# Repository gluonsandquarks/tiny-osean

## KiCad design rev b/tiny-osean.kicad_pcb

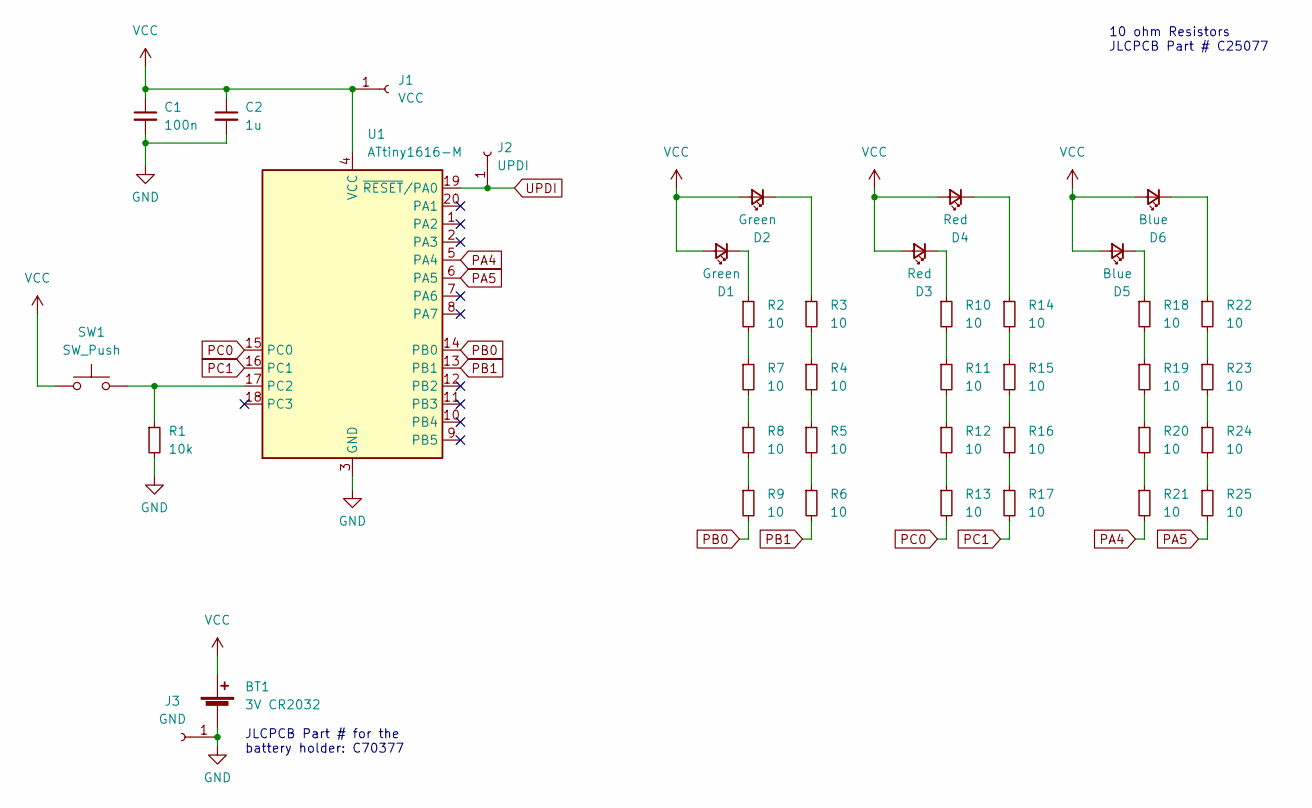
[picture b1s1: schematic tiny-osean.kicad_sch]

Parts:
BT1: 3V CR2032; CR2032 Holder; LCSC C70377
C1: 100n; C_0402_1005Metric; LCSC C307331
C2: 1u; C_0603_1608Metric; LCSC C15849
D1, D2: Green; C_0805_2012Metric_Pad1.18x1.45mm_HandSolder; LCSC C2296
D3, D4: Red; C_0805_2012Metric_Pad1.18x1.45mm_HandSolder; LCSC C2296
D5, D6: Blue; C_0805_2012Metric_Pad1.18x1.45mm_HandSolder; LCSC C2296
J1: VCC; PinHeader_1x01_P2.54mm_Vertical
J2: UPDI; PinHeader_1x01_P2.54mm_Vertical
J3: GND; PinHeader_1x01_P2.54mm_Vertical
R1: 10k; R_0603_1608Metric; LCSC C25804
R2, R3, R4, R5, R6, R7, R8, R9, R10, R11, R12, R13, R14, R15, R16, R17, R18, R19, R20, R21, R22, R23, R24, R25: 10; R_0402_1005Metric; LCSC C25077
SW1: SW_Push; SW_Push_1P1T_NO_CK_KSC6xxJ; LCSC C318884
U1: ATtiny1616-M; VQFN-20-1EP_3x3mm_P0.4mm_EP1.7x1.7mm; LCSC C507118

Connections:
GND: BT1.2 (-), C1.2, C2.2, J3.1, R1.2, U1.3 (GND), U1.21 (GND)
unnamed: D1.1 (K), R2.1
unnamed: D2.1 (K), R3.1
unnamed: D3.1 (K), R10.1
unnamed: D4.1 (K), R14.1
unnamed: D5.1 (K), R18.1
unnamed: D6.1 (K), R22.1
unnamed: R1.1, SW1.2, U1.17 (PC2)
unnamed: R3.2, R4.1
unnamed: R4.2, R5.1
unnamed: R5.2, R6.1
unnamed: R2.2, R7.1
unnamed: R7.2, R8.1
unnamed: R8.2, R9.1
unnamed: R10.2, R11.1
unnamed: R11.2, R12.1
unnamed: R12.2, R13.1
unnamed: R14.2, R15.1
unnamed: R15.2, R16.1
unnamed: R16.2, R17.1
unnamed: R18.2, R19.1
unnamed: R19.2, R20.1
unnamed: R20.2, R21.1
unnamed: R22.2, R23.1
unnamed: R23.2, R24.1
unnamed: R24.2, R25.1
PA4: R21.2, U1.5 (PA4)
PA5: R25.2, U1.6 (PA5)
PB0: R9.2, U1.14 (PB0)
PB1: R6.2, U1.13 (PB1)
PC0: R13.2, U1.15 (PC0)
PC1: R17.2, U1.16 (PC1)
UPDI: J2.1, U1.19 (~RESET/PA0)
VCC: BT1.1 (+), C1.1, C2.1, D1.2 (A), D2.2 (A), D3.2 (A), D4.2 (A), D5.2 (A), D6.2 (A), J1.1, SW1.1, U1.4 (VCC)

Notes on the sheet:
10 ohm Resistors JLCPCB Part # C25077
JLCPCB Part # for the battery holder: C70377

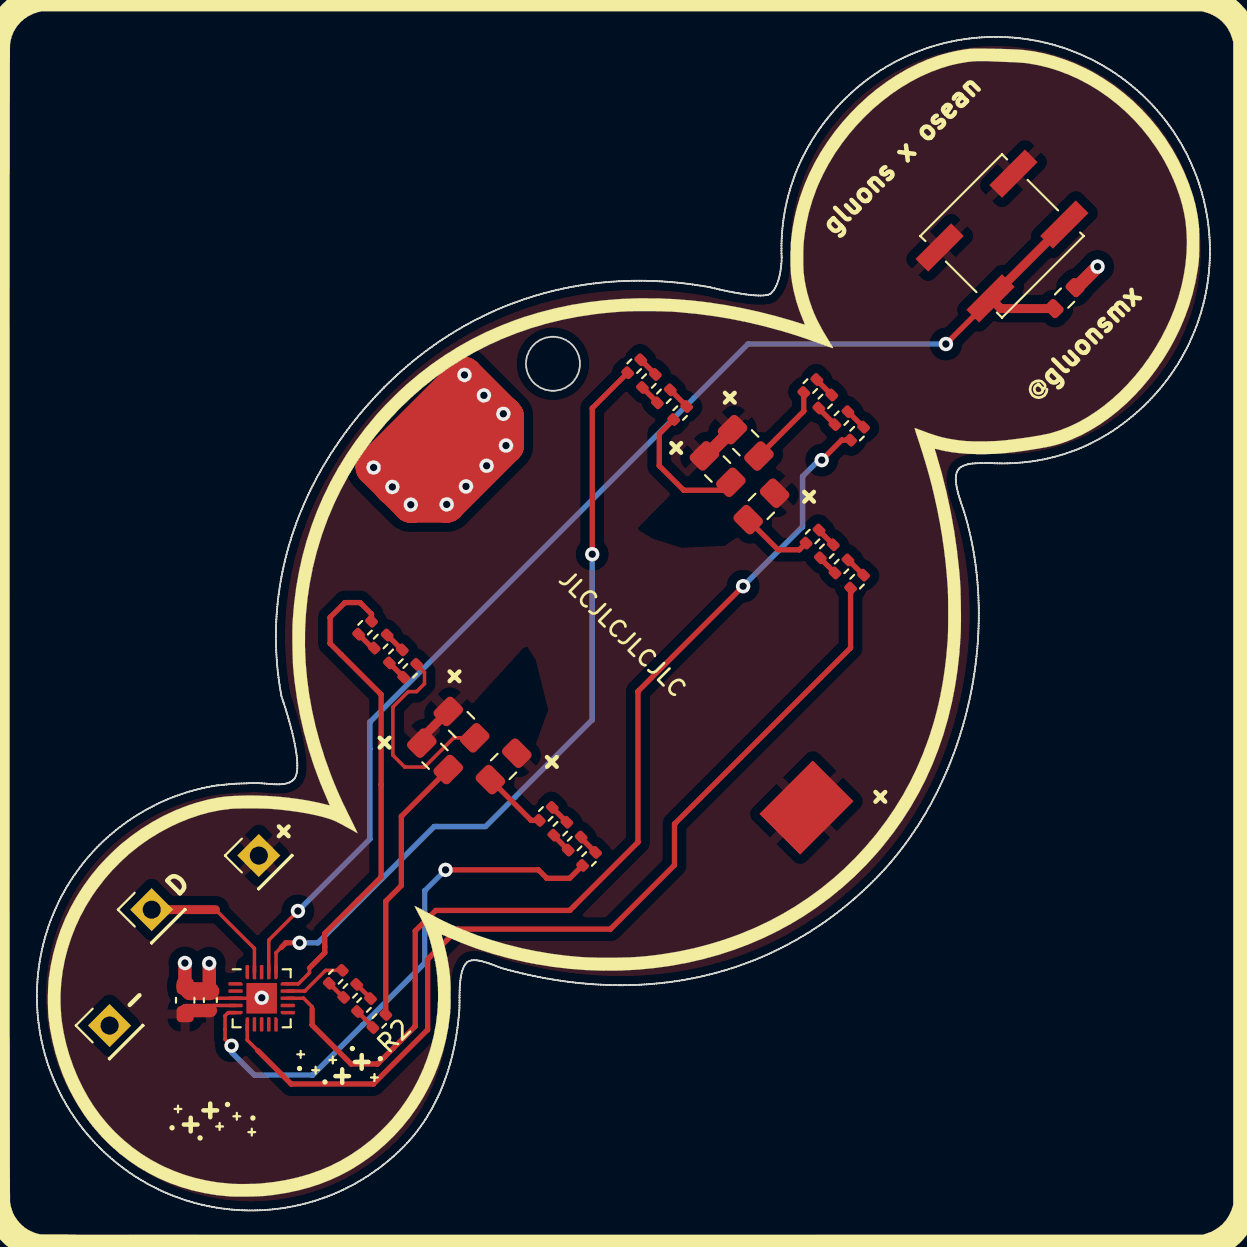
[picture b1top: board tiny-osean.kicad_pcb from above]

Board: 2 copper layers, 65.2 x 65.2 mm, 40 parts (0 on the bottom side), 34 nets.

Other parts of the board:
Ref**: Val**; tiny-osean-70

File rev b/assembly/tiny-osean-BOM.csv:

Comment,Designator,Footprint,LCSC
"3V CR2032","BT1","tiny-osean:CR2032 Holder","C70377"
"100n","C1","Capacitor_SMD:C_0402_1005Metric","C307331"
"1u","C2","Capacitor_SMD:C_0603_1608Metric","C15849"
"Yellow","D1,D2","Capacitor_SMD:C_0805_2012Metric_Pad1.18x1.45mm_HandSolder","C2296"
"VCC","J1","Connector_PinHeader_2.54mm:PinHeader_1x01_P2.54mm_Vertical",""
"UPDI","J2","Connector_PinHeader_2.54mm:PinHeader_1x01_P2.54mm_Vertical",""
"GND","J3","Connector_PinHeader_2.54mm:PinHeader_1x01_P2.54mm_Vertical",""
"SolderJumper_2_Open","JP1,JP2","Jumper:SolderJumper-2_P1.3mm_Open_TrianglePad1.0x1.5mm",""
"10k","R1","Resistor_SMD:R_0603_1608Metric","C25804"
"10","R2,R3,R4,R5,R6,R7,R8,R9","Resistor_SMD:R_0402_1005Metric","C25077"
"SW_Push","SW1","Button_Switch_SMD:SW_Push_1P1T_NO_CK_KSC6xxJ","C318884"
"ATtiny1616-M","U1","Package_DFN_QFN:VQFN-20-1EP_3x3mm_P0.4mm_EP1.7x1.7mm","C507118"

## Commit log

2022-10-29 Final Rev A
2022-11-09 added images and a quick description
2022-11-15 added basic firmware & jtag2updi
2022-11-16 added more light shows and a sleep mode, need to document the functions and stuff
2022-11-16 research to be done on avr/sleep.h implementation
2022-11-16 fixed minor formatting
2022-11-16 added more info to README.md
2022-11-16 added more info
2022-11-16 addde license
2022-11-16 fixed owner lol
2022-11-22 started rev b
2022-11-29 finished rev b in one night cause discounts dont last forever
